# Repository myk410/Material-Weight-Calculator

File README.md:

# Material Weight Calculator

A standalone pocket calculator for estimating material weight. Select a material, enter length, width, and thickness in inches, and read the result in pounds. Runs entirely on one microcontroller with physical buttons and replaceable AAA batteries.

Status: **R3 LTC3440 buck-boost PCB implemented and CAD-validated, November 12, 2026; FABRICATION HOLD.** See [R3 review, evidence and unresolved physical checks](hardware/R3_REVIEW.md) and open [the R3 KiCad project](hardware/pcb/r3/material_weight_calculator.kicad_pro). Both current R3 boards use SMD resistors, capacitors, transistors, diodes and inductors; the purchased AVR DIP/socket and connectors are retained. See [owned-parts policy](hardware/OWNED_PARTS_AND_SMD.md). Main and display-adapter boards pass KiCad 9 ERC, DRC and schematic parity with zero violations. No R3 Gerbers/drills/order ZIP have been released because real-part mating and fit checks remain open. Existing R2 manufacturing archives use MCP1700 and must not be ordered as R3. Firmware, prototype operation and battery life remain untested.

## Proposed final low-power hardware

| Part | Proposed choice | Reason |
| --- | --- | --- |
| Controller | Microchip AVR128DA28, preferably the through-hole package for a hand-built prototype | One low-power microcontroller; enough RAM for a graphical display; internal oscillator; no wireless hardware needed |
| Display | EastRising ERC12864FS-655, 2.8-inch 128 × 64 positive monochrome LCD, no touch panel | Larger black-on-light screen; operate with backlight disconnected; separate UC1701 adapter PCB included |
| Buttons | Sixteen flexible-resin button caps over the user-owned DIYmalls 4 × 4 membrane keypad | Sixteen physical keys using eight controller pins; no separate keypad processor |
| Batteries | Three AAA alkaline cells in a replaceable holder | Switched supply; buck-boost conversion extends useful battery range, subject to diode drop and sag |
| Regulator | LTC3440EMS#PBF, MSOP-10, R3 | Nominal 3.3 V buck-boost with hand-solderable SMD supply components; see the R3 review for qualification limits |
| Supporting parts | Regulator input/output capacitors, local MCU decoupling, battery protection diode, display power transistor, service link, programming header | Reliable supply and a way to program the controller without leaving a USB interface powered |
| Housing | Rigid-resin printed calculator enclosure with accessible battery compartment | Large readable labels and easy battery replacement |

See [PARTS_LIST.md](PARTS_LIST.md) for previously purchased parts and the prototype route. The exact hardware R2 component and M2.5 fastener lists are in [hardware/README.md](hardware/README.md). The current R2 design uses the 70 × 50 mm EastRising display and a 70 × 18 mm adapter. The manufacturer lists up to 500 µA LCD current at 3.3 V; complete-device current and indoor readability still require a physical test.

The AVR128DA28 has 16 KB SRAM. A 128 × 64 monochrome framebuffer needs 1,024 bytes. PA1/PA2/PA3 drive clock/data/chip select, PA4 selects command/data, and PA5 resets the UC1701. The device needs firmware; the HTML calculator is a separate working example.

## Why memory LCD instead of e-paper?

| Display | Suitability |
| --- | --- |
| Reflective memory LCD | Recommended for calculator entry: quick digit updates, low power, readable by reflected light. Requires power and periodic display polarity inversion while displaying an image. |
| Black-and-white e-paper | Excellent for holding a result with display power removed. Updates are slower and may show ghosting or occasional full-screen flashes; partial-refresh behavior depends on the exact panel. |
| Reflective character LCD without a backlight | Worth considering if a cheaper, simpler text-only display is preferred. Select a specific low-power module before comparing total current; ordinary hobby modules are not all equally efficient. |

E-paper is compatible with a microcontroller and does not require a Raspberry Pi. For this device, fast keypad feedback makes memory LCD the stronger starting point. Neither unlit option is readable in darkness without external light.

## User operation

1. Press ON to wake the calculator.
2. Use MENU for material selection; 8/↑ and 2/↓ move through menus and ENTER selects. Default to the last material during the current powered session.
3. Choose solid rectangular stock or pipe using a short menu on the existing keypad.
4. For rectangular stock, enter length, width, and thickness in inches.
5. For pipe, enter length, actual outside diameter, and wall thickness (or inside diameter). Press ENTER after each input.
6. Show the material, dimensions, and estimated pounds, with the weight in the largest text.

Key functions: digits 0–9, decimal point, ENTER, MENU, BACK, CLEAR, and ON/OFF. This fits a 16-key matrix. The printed button caps will be made in rubbery resin, with recessed legends, and will actuate electrical switches underneath. See [MECHANICAL_DESIGN.md](MECHANICAL_DESIGN.md) for the key layout and printing requirements.

BACK deletes the last digit; with an empty field it returns to the previous field. CLEAR empties the current entry; on the result screen it starts a new piece while retaining the selected material and shape. ON/OFF puts the calculator to sleep. Do not use long-press combinations for routine entry. Start with decimal inches; fraction entry can be added if needed after testing the controls.

Reject empty fields, zero or negative dimensions, malformed numbers, overflow, and values beyond the supported input range. Display an explicit error instead of a plausible-looking weight. Always label the result as an estimate.

## Calculation and material data

For a solid rectangular piece:

`weight_lb = length_in × width_in × thickness_in × density_lb_per_ft3 / 1728`

Example using the published carbon-steel density of 7,850 kg/m³ (about 490.059 lb/ft³): a 12 × 12 × 1-inch plate weighs about 40.838 lb, displayed as `40.84 lb`.

The HTML now supports rectangular stock, pipe/round tube, and known volume. Pipe volume is `π × wall × (OD − wall) × length`, or equivalently `π/4 × (OD − ID) × (OD + ID) × length`. All dimensions are in decimal inches. Use actual diameters, not nominal pipe sizes. Pipe results exclude contents and fittings. Other hollow profiles and irregular parts need their own formulas.

At the user’s direction, the calculator replaces the company card values with published grade-specific densities. Material names now identify the grade, and separate presets cover LDPE/HDPE, 304/316 stainless, 718/625 nickel alloys, and 90/10 or 70/30 CuNi. Density overrides remain available for other grades. See [DENSITY_REVIEW.md](DENSITY_REVIEW.md) for active values, sources, and the historical card comparison. Do not use a broad material family as if every grade had the same density.

The handheld firmware should provide the same shape choices and density policy. Device firmware has not yet been implemented; the hardware pin map and power-control requirements are documented in hardware/README.md.

## Battery and sleep design

R3 uses three AAA alkaline cells through the physical slide switch, SS14 polarity diode and LTC3440 buck-boost supply. The regulated nominal output is 3.294 V. The converter's 2.5 V minimum applies at its VIN pin **after diode loss and battery sag**. The current EastRising UC1701 display is supplied from this rail through Q1; it has no Sharp-breakout regulator in this path.

The LTC3440's typical Burst Mode quiescent current is 25 µA, and the output divider adds about 6.1 µA. R3 therefore does not meet the old sub-10-µA automatic-sleep goal with its rail running; MCU and other leakage add to this. The slide switch provides hard battery disconnection. Whole-device current, stability and runtime remain unmeasured.

- While active, scan/debounce keys and update the UC1701 framebuffer. This display does not use the former Sharp memory-LCD VCOM servicing scheme.
- After about two minutes without input, save current state in RAM, blank the display, shut the display down according to its documentation, disable unused peripherals, and enter MCU power-down mode.
- If display power is switched off, put connected signal pins in a safe state to prevent back-powering. Reinitialize and redraw on wake.
- Wake from a keypad interrupt. In sleep, drive matrix columns low and use pulled-up interrupt-capable row inputs. Confirm exact AVR pin wake behavior before assigning pins. Consume the wake press so it does not enter a stray digit. Wait for key release before accepting another entry.
- Avoid continuous keypad polling during sleep, always-on LEDs, powered USB adapters, and continuously connected battery-sense resistor dividers.
- The case-mounted CYT1107 slide switch disconnects battery positive before main-board J2 pin 1; battery negative goes to J2 pin 2. JP1 remains an internal service link with its shunt normally fitted. The keypad ON/OFF key controls sleep only while the slide switch is ON. Hard power-off loses RAM state. See [power-switch wiring](hardware/POWER_SWITCH.md).

Battery-life estimates must use measured current for the complete assembly, including converter, divider, MCU and display. The former sub-10-µA automatic-sleep target is superseded by the R3 supply budget above; active current is also unverified.

Illustrative budget only: at 5 mA for 20 minutes per day plus 10 µA for the rest of the day, consumption is about 1.90 mAh/day. An assumed usable pack capacity of 800 mAh gives about 420 days arithmetically. Real runtime will depend on cutoff voltage, cell type, regulator dropout, temperature, leakage, and usage. Series-connected AAA cells raise voltage; their mAh capacities do not add.

## Build sequence

1. Confirm a readable display size and source the exact module.
2. Prototype the controller, display, and relabeled keypad. Use a detachable UPDI programmer; it is a setup tool, not part of the running device.
3. Implement the material menu, three input fields, calculation, and input validation. Check known rectangular-stock examples and custom density.
4. Implement keypad wake and display shutdown. Measure whole-device active and sleep current from the battery input.
5. Validate operation over the usable battery voltage range, including low-battery indication and clean handling of power loss.
6. Finalize the schematic, component list, firmware build instructions, and enclosure after these checks.

## Manufacturer references

- [Microchip AVR128DA28](https://www.microchip.com/en-us/product/AVR128DA28) and its linked datasheet: voltage limits, memory, sleep behavior, pin functions, and programming.
- [Analog Devices LTC3440](https://www.analog.com/en/products/ltc3440.html) and its linked datasheet: R3 regulator topology, pinout, compensation, layout and high-input protection. The preserved R2.1 design used MCP1700.
- [Waveshare e-paper manual](https://www.waveshare.com/wiki/2.13inch_e-Paper_HAT_Manual): refresh and standby considerations for an alternative display.
- [ATI corrosion-resistant titanium datasheet](https://www.atimaterials.com/Products/Documents/datasheets/titanium/alloyed/ati_corrosion_resistant_titanium%20_alloys_tds_en5_v1.pdf): grade-specific titanium density.

## Validation

Run `node tests/calculator.test.cjs` to check rectangular and pipe formulas, equivalent wall/ID inputs, published grade densities and replacement of the titanium misprint, input validation, override labeling, and mocked UI transitions. These checks pass. A real-browser check could not run in the current environment because the Chromium executable is unavailable; browser rendering and physical hardware remain unverified.

The display pin map, electrical source references, adapter BOM and 128 × 64 screen-layout requirements are in [hardware/DISPLAY_INTEGRATION.md](hardware/DISPLAY_INTEGRATION.md).

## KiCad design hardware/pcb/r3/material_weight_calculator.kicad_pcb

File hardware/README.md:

# Material Weight Calculator — current R3 review

**FABRICATION HOLD.** The current LTC3440 MSOP-10 design is in [pcb/r3](pcb/r3/material_weight_calculator.kicad_pro). Read [R3_REVIEW.md](R3_REVIEW.md) for the circuit, actual KiCad results, both-side orientation templates, BOM and required physical evidence. Both current R3 boards use SMD resistors, capacitors, transistors, diodes and inductors; the purchased AVR DIP/socket and connectors are retained. See [owned-parts policy](OWNED_PARTS_AND_SMD.md). Main/adapter ERC, DRC and schematic parity pass with zero violations. No R3 Gerbers, drills or order ZIP are released. The R2 files and links below are historical MCP1700 designs, not the R3 supply, and must not be used for this redesign.

## Historical R2.1 documentation

PCB review updated November 2, 2026: [review, evidence and assembly gates](PCB_REVIEW.md). Open the reviewed PCB files with **KiCad 9 or newer**. The download filenames retain `r2` for existing links; their fabrication contents identify R2.1. Mechanical files retain their separate revision history.

This package contains real parametric CAD, printable STLs, a routed KiCad PCB, schematic, Gerbers, drills, and actual-scale print templates. It is a **prototype design**, not a physically tested or production-qualified assembly. The device firmware is not included in this hardware release; its revised 128 × 64 display and sleep requirements are specified in DISPLAY_INTEGRATION.md. R2 replaces the small Sharp display. R1 files remain in Git history, not in current print/download folders.

Download [complete R2 package](downloads/material_weight_calculator_hardware_r2.zip) or [both PCB fabrication sets](downloads/pcb_fabrication_r2.zip).

## Start here

1. Open `docs/case_front_preview.png` to inspect the actual CAD and recessed legends.
2. Print `docs/keypad_fit_template.pdf` at **100% / Actual Size**. Place the existing DIYmalls pad over the key-center marks. The screenshot identifies the pad type but does not establish its exact pitch. The model currently uses nominal 18 mm key pitch; confirm this fit before printing the full shell. The source has explicit `KEY_X` and `KEY_Y` parameters if the actual pad differs.
3. Print the two-key connected 55A keypad coupon before the full keypad sheet. Check legend detail, independent motion, return, actuator contact, nut fit, and actuation with the actual DIYmalls membrane. No claim is made that the 55A resin's force, shrinkage, or long-term fatigue has been physically validated yet.
4. For the Mars 5 Ultra, use the shell sections in `stl/mars5_ultra_oriented/`. They have been rotated to fit the manufacturer's 153.36 × 77.76 × 165 mm build volume; add supports and a raft in the slicer without exceeding that volume. These are unsliced STLs, not exposure profiles.
5. Historical R2.1 only; **do not order these for R3**. `pcb/gerbers/` describes a conventional **two-layer, 1.6 mm copper-clad PCB with plated through holes**. Open the KiCad project to inspect/edit it before ordering.

## Files

| Location | Contents |
| --- | --- |
| `stl/` | Four case sections, battery cover, keypad plates, display cradle, **one-piece 55A flexible keypad sheet**, and fit coupons |
| `stl/mars5_ultra_oriented/` | Printer-fitting orientations for the shell sections and larger keypad plates |
| `cad/calculator_assembly.step` | Assembly with parts in their assembled locations; split case sections included |
| `cad/pcb_outline.step` | Board outline and four mounting holes, matching the enclosure |
| `cad/*whole_reference.stl` | Unsplit shell references for a larger printer; do not use these on the Mars 5 Ultra |
| `source/build_case.py` | Editable CadQuery source for case, one-piece keypad sheet, nut pockets, and split shells |
| `pcb/material_weight_calculator.kicad_pro` | KiCad 9 project |
| `pcb/material_weight_calculator.kicad_sch` | Editable, embedded-symbol schematic with every used pin/net explicitly named |
| `pcb/material_weight_calculator.kicad_pcb` | Routed two-layer board, 82 × 68 mm |
| `pcb/mw-footprints.pretty/` | Bundled standard footprints; project does not depend on an external footprint-library path |
| `pcb/gerbers/` | Top/bottom copper and masks, top silkscreen, outline, separate plated/non-plated Excellon drills and SVG drill maps |
| `docs/copper_artwork_1to1.pdf` | Exact KiCad copper plots: top reference, top transfer, bottom reference, bottom transfer |
| `docs/drill_template.pdf` | Component-side drill and board outline template |
| `docs/keypad_fit_template.pdf` | Full-scale membrane alignment template and 100 mm scale check |
| `docs/schematic.pdf` | Circuit drawing exported by KiCad |
| `pcb/bom.csv` | Main-board BOM |
| `pcb/display_adapter/` | Second KiCad project, schematic, routed 70 × 18 mm adapter and BOM |
| `docs/display_adapter_schematic.pdf` | Adapter circuit, exported by KiCad |
| `docs/display_adapter_copper_1to1.pdf` | Four actual-scale copper reference/transfer pages |
| `docs/display_adapter_drill.pdf` | Adapter drill/outline template at actual size |
| `docs/display_fit_template.pdf` | Full-scale 70 × 50 mm module and pin-center alignment check |
| `DISPLAY_INTEGRATION.md` | Authoritative R2 display pin map, sources and firmware requirements |
| `validation/` | CAD, mesh, schematic-net and KiCad design-rule reports |

The STLs are in millimeters, not mirrored. Each individual file is translated to its own positive bounding box. Use STEP for assembly positions. The old loose-button aggregate `all_16_buttons.stl` is obsolete; rebuilding the current source deletes it and exports `keypad_sheet_55A.stl` instead. No support structures are baked into the meshes.

## One-piece 55A keypad

The custom visible keypad is now **one connected flexible-resin part**, not sixteen loose buttons. The CAD nominally uses a 72 × 72 × 0.85 mm continuous sheet behind the 4 × 4 button field. Each key has a 14 × 14 mm top rising about 5 mm above that sheet, plus a centered smooth 8 mm-diameter actuator projecting about 1.55 mm below it.

The thin sheet is the flex zone. The thicker key tops remain individual islands geometrically, but they are permanently joined by the 0.85 mm membrane. This should reduce assembly parts, keep the key field aligned, and provide a continuous dust barrier over the original electrical membrane. The dimensions are prototype targets and should be tuned after the first real 55A print.

The existing DIYmalls 4 × 4 pad remains the **electrical switch layer** underneath. The printed 55A part is only the custom mechanical keypad. Do not assume the printed resin is conductive.

## Case and fasteners

Overall body: 96 × 184 × 31 mm, with button tops at about 33 mm. Wall/face thickness is generally 2.6 mm, with internal reinforcement webs. The PCB's lower face is 7 mm from the rear reference plane. The holder pocket targets a Pololu 1144-style 52 × 37 × 13 mm three-AAA holder with leads, allowing clearance around that envelope.

All fastening provisions are **M2.5 with hex nuts**, as requested. Nominal nut pockets are 5.35 mm across flats and about 2.45 mm deep; clearance holes are 2.9 mm. Glue nuts around their outside faces, keeping threads and screw paths clean. On front-facing pocket openings, hold the nut flush to the pocket's open face while the adhesive sets, rather than pushing it deeper into the clearance allowance. Verify actual nut dimensions with the coupon before gluing the full set.

| Joint | Screws | Nuts |
| --- | --- | --- |
| Rear to front shell | 4 × M2.5 × 16 mm | 4, glued into front-shell pockets |
| PCB to rear posts | 4 × M2.5 × 6 mm | 4, glued into rear-post pockets |
| Keypad backing + guide stack to front | 4 × M2.5 × 6 mm | 4, glued into front pockets |
| Display cradle to front | 4 × M2.5 × 6 mm | 4, glued into front pockets |
| Battery cover | None; sliding rails and snap latch | None |

Total: **16 nuts; four 16 mm and twelve 6 mm screws**. Screw lengths are measured under the head. Trial-fit and shorten any screw that bottoms before clamping; do not force a screw into resin. The design does not use heat-set inserts or self-tapping threads.

The long front and rear shells each have an upper/lower **bonded seam** at plan Y=60.25 mm, with locating tongues and mating relief. Bond each upper/lower pair into one shell before final assembly. This printing seam is separate from the removable, screwed front/rear joint. Use an adhesive appropriate for the fully cured rigid resin and test it on a coupon. One-piece references are included if a larger printer is available.

## Assembly order

1. Wash/cure the printed parts according to the actual resin's instructions. Clear supports from recesses and mating faces. Bond the two front sections and the two rear sections using their locating features.
2. Test-fit and glue the M2.5 nuts into their pockets. Allow adhesive to set before applying screw load.
3. From inside the front, place the **single connected 55A keypad sheet** behind all sixteen bezel openings at once. Align its sixteen button tops with the openings. The 0.85 mm connecting membrane remains behind the bezel and keeps the entire keypad registered as one piece. Legends are actual 0.4 mm Boolean recesses, not rendered textures.
4. Install the rigid guide/backing stack and the existing DIYmalls electrical membrane underneath the printed keypad. The guide acts as registration and a travel-stop layer while the thin printed sheet provides key return. The current actuator projection and rest/stop values are prototype geometry only; verify that the electrical pad is not preloaded at rest and that each key returns without dragging its neighbors.
5. Route the electrical membrane's flexible ribbon through the backing relief; avoid sharp folds or pinching at the enclosure edge. The backing's screw slots allow small translational adjustments, not arbitrary correction of key pitch.
6. Use the ERC12864FS-655 **without touch panel**. Its body fits at plan (13,7.5), 70 × 50 × 5.8 mm maximum. The 67 × 37 mm bezel opening follows the drawing's viewing-area offset: 1.5 mm from the left and 3.5 mm from the top. Place thin 0.5 mm closed-cell foam on opaque perimeter/frame surfaces, between the front shell and module and between the module's backlight frame and rear cradle. Fit the cradle with four M2.5 × 6 mm screws. Tighten only enough to retain it; do not compress LCD glass, the polarizer or the solder tail. No separate printed edge clamps are used in R2.
   Assemble the display adapter before installing the cradle. J2 is a **1×22 row at 1.27 mm pitch**, not 2.54 mm. Solder the module's own pins directly into the adapter holes; do not add another tall header/socket. Keep the adapter at nominal Z=13 to 14.6 mm behind the top tail. Check pin-1 orientation against the manufacturer's front-view drawing. Use short insulated wires at adapter J1 rather than a tall plug. Secure the cable to the cradle side with a soft tie/adhesive anchor, without loading the glass. Capacitor C5 must be ≤4 mm diameter and ≤7 mm high; C1/C2 ≤5.5 mm high and remaining adapter parts ≤5 mm high. Confirm actual pin reach before soldering; the fit template provides the 22 pin centers.
7. Assemble the PCB, check power rails with U1/display disconnected, fit the socketed MCU, then connect the keypad, display cable, and battery holder using the wiring below.
8. Install the PCB in the rear tray, secure the battery holder in its pocket, and route leads clear of nut pockets and ribs. Install the battery cover, then join front/rear with the four longer screws.

## PCB circuit and parts

| Ref | Part / function | Quantity |
| --- | --- | ---: |
| U1 | AVR128DA28-I/SP, in 28-pin narrow DIP socket (7.62 mm row spacing) | 1 + socket |
| U2 | MCP1700-3302E/TO, 3.3 V LDO; spread-lead TO-92 footprint | 1 |
| D1 | 1N5817, DO-41, battery reverse-polarity protection | 1 |
| Q1 | onsemi 2N3906 PNP, E-B-C pins 1-2-3, TO-92 spread leads; switches display power | 1 |
| R1 | 10 kΩ, axial, 7.62 mm lead spacing | 1 |
| R2 | 100 kΩ, axial, 7.62 mm lead spacing | 1 |
| C1, C2, C5 | TDK FG14X7R1H225KRT00, 2.2 µF 50 V X7R, 2.5 mm pitch; body ≤4.5 × 3.0 mm, height ≤5.5 mm | 3 |
| C3, C4 | 100 nF, at least 10 V, ceramic, 2.5 mm lead spacing | 2 |
| J1 | 1×8, 2.54 mm male header to existing keypad tail | 1 |
| J2 | 1×2, 2.54 mm battery-lead connector; observe polarity | 1 |
| JP1 | 1×2, 2.54 mm header and shunt, normally fitted master/service link | 1 |
| J3 | 1×8, 2.54 mm header to display via cable | 1 |
| J4 | 1×3, 2.54 mm UPDI programming header | 1 |
| External | Existing membrane keypad, ERC12864FS-655 display and R2 adapter, three-AAA holder and cells, wiring | 1 set |

No USB interface, radio, indicator LED or charging circuit is on this board. It uses alkaline AAA cells. D1 adds a small forward drop, so regulation ends earlier in battery discharge than with an ideal-diode design. The case-mounted CYT1107 slide switch is the primary hard ON/OFF control, wired before J2 pin 1; J2 pin 2 is battery negative. JP1 remains a normally fitted internal service link. The keypad ON/OFF key provides sleep/wake only while hard power is ON. See POWER_SWITCH.md. Hard OFF removes the battery source, but a connected powered UPDI programmer can still power the board.

Q1 is off at reset through R2. Firmware must drive U1 PD7 **low** to enable display power and **high** to turn it off. Before removing display power, drive all display signal outputs low to prevent back-powering, then redraw/reinitialize on wake. UC1701 maintains LCD drive internally while powered; no Sharp-style VCOM servicing is used. Reset and reinitialize the UC1701 after each display power cycle. Use PA4 for command/data and PA5 for active-low LCD reset. Disable unused peripherals and configure unused MCU pins appropriately; whole-device sleep current is not yet measured.

### Connector wiring

J1 pins 1–4 are assigned ROW0–ROW3 on PC0–PC3; pins 5–8 are COL0–COL3 on PD0–PD3. Membrane tail row/column ordering varies: establish the actual mapping by continuity test or a key-scan test, then map the eight signal assignments in firmware. Do not assume the photo supplies the electrical pinout.

| Main J3 / adapter J1 pin | Function | MCU |
| ---: | --- | --- |
| 1 | Switched 3.3 V LCD_VCC | Q1 collector |
| 2 | GND | Ground |
| 3 | SCK | PA1, DIP pin 23 |
| 4 | SDA | PA2, DIP pin 24 |
| 5 | CS, active low | PA3, DIP pin 25 |
| 6 | CD: low command, high pixels | PA4, DIP pin 26 |
| 7 | RST, active low | PA5, DIP pin 27 |
| 8 | No connection; spare position | No wire |

Connect matching **pin numbers** between main J3 and adapter J1. These are seven wires on an eight-position footprint. No part of this cable is compatible with R1's Sharp wiring. The adapter straps BM1/BM0, WR0/WR1 and unused D0–D5 to ground, and provides the LCD charge-pump capacitors. Leave the separate backlight A/K terminals insulated and unconnected.

Adapter BOM: C1/C2 = TDK FG14X7R1H225KRT00, 2.2 µF 50 V X7R (2.5 mm pitch, 4.5 × 3.0 mm body, height ≤5.5 mm), C3 = 330 nF 25 V ceramic, C4 = 100 nF, C5 = 10 µF 16 V low-leakage electrolytic (4 mm diameter, 1.5 mm pitch, ≤7 mm height), R1 = 10 MΩ axial. The two flying capacitors bridge VB0+/VB0− and VB1+/VB1−; C3 and R1 connect VLCD to ground. See the separate adapter schematic, BOM and DISPLAY_INTEGRATION.md.
J4 pin 1 is +3.3 V / VTREF, pin 2 GND, pin 3 UPDI. A suitable example programmer is **Adafruit UPDI Friend 5879**, set to **3V**. Disconnect the AAA pack when powering the target from the programmer. Do not connect two independent supplies together. The CANADUINO ATmega328P automatic bootloader programmer is not compatible with this MCU.

### Existing pad labels to custom keys

| Original pad row | Custom button functions in the same physical positions |
| --- | --- |
| 1, 2, 3, A | 7, 8/Up, 9, MENU |
| 4, 5, 6, B | 4, 5, 6, BACK |
| 7, 8, 9, C | 1, 2/Down, 3, CLEAR |
| *, 0, #, D | ON/OFF, 0, decimal point, ENTER/= |

## Fabrication and printing

For a PCB manufacturer, use the Gerbers and separate PTH/NPTH drill files, specify **82 × 68 mm, 2 layers, 1.6 mm FR-4**, and retain plated holes. Fabricate the **70 × 18 mm adapter** as a separate 2-layer, 1.6 mm FR-4 board from `pcb/display_adapter/gerbers/`. The fabrication ZIP has a separate directory for each board; do not combine their layers. All tracks are 0.4 mm wide; minimum configured clearance is 0.25 mm; both boards use through vias, 1.0 mm diameter / 0.5 mm drill (actual counts in their design JSON files). Standard footprint holes retain their own drill diameters. The board mounting holes are 2.7 mm nominal; the resin clearance holes are 2.9 mm.

For home etching, the copper PDF includes labeled reference and transfer orientations. Print 100%, verify the 100 mm scale, and register both layers accurately. Home-drilled holes are not automatically plated: every via and any PTH joining layers requires a conductive connection soldered on both sides. DIP sockets and headers can obstruct top-side soldering, so use accessible raised/machined contacts or a professionally plated board. Exact Gerbers are authoritative; the PDFs are for manual processes.

Ordinary printing resin forms the housing and keypad, **not conductive PCB traces**. The PCB files describe copper on an insulating board. No resin-printer exposure file, printer-specific sliced file, or CNC isolation toolpath is supplied because those depend on the actual fabrication process and tools.

The STLs are unsliced. Use rigid resin for housing, cradle and plates; use **55A flexible resin for `keypad_sheet_55A.stl`**. Keep supports away from label recesses, screw bores, nut pockets, actuator faces and mating surfaces. The keypad sheet is only 0.85 mm thick between keys, so avoid support placement or cleanup methods that can tear or permanently distort the flex zones. Optional compatible paint-fill can improve legend contrast. Hollow shell cavities must remain accessible for washing and curing; orient them to drain.

## What was verified

- Each individual CAD part in the prior R2 build was a valid, single solid.
- Each exported STL in the prior R2 build had a closed two-use edge graph at the mesh-check precision.
- Pairwise assembled-part checks in the prior R2 build found no positive intersections above 0.02 mm³ (nominal, unloaded geometry).
- Exported schematic pin-to-net connections match the PCB design definition, normalizing the root-sheet prefix on local net names.
- R2.1 KiCad 9.0.2 reports: **0 ERC violations, 0 DRC violations, 0 unconnected items and 0 schematic parity issues**, on both boards. Symbols have electrical pin types and bundled project libraries. See `validation/pcb_audit.json` for the actual-pad/copper and case-hole audit.
- PCB outline/mount-hole positions and case PCB posts share the same design coordinates.
- **The new one-piece 55A keypad source has not yet been physically printed or re-validated as an exported mesh in this commit.** Rebuild the CAD and inspect `validation/cad_checks.json` before treating the generated keypad STL as final.
- Actual keypad pitch, cured-resin tolerances, membrane actuation, display pin fit/ambient-light contrast, soldered component heights, electrical operation and battery runtime still need physical confirmation. Computational checks do not replace an electrical bench test or an independent hardware review.

## Rebuilding

Use CadQuery 2.7 / OpenCascade for `python source/build_case.py`. The current source exports `stl/keypad_sheet_55A.stl`, a two-key 55A fit coupon, and removes obsolete loose-button STLs from older builds. `source/check_and_render.py` also rebuilds the CAD, checks meshes and net mappings, and draws previews. For the current reviewed boards, run `source/refresh_schematics.py`, then `source/export_pcbs.py` and `source/audit_pcb.py` using KiCad 9 Python bindings and CLI. The original `build_pcb.py` and `build_display_adapter.py` routing generators rebuild copper from scratch and call the schematic refresh afterward; a fresh routed build requires a new full audit. Prefer refresh for metadata/schematic changes so the reviewed copper is retained. Run `source/validate_display.py` for the manufacturer pin/capacitor audit. Export both schematic netlists before running the net checks. `source/plot_copper.py` uses KiCad's native plot controller for exact copper artwork. `source/make_print_templates.py` requires ReportLab. Plot main copper with `source/plot_copper.py`, then again with `DISPLAY_ADAPTER=1`; run `source/finish_exports.py` last to assemble labeled PDFs, verify both netlists and package R2 ZIPs.

## Source references

- [AVR128DA28 datasheet, pinout and SPDIP package](https://ww1.microchip.com/downloads/aemDocuments/documents/MCU08/ProductDocuments/DataSheets/AVR128DA28-32-48-64-Data-Sheet-DS40002183.pdf).
- [MCP1700 datasheet, TO-92 pinout and capacitor requirements](https://ww1.microchip.com/downloads/en/DeviceDoc/MCP1700-Data-Sheet-20001826F.pdf).
- [ERC12864FS-655 product](https://www.buydisplay.com/2-8-inch-128x64-graphic-module-serial-display-spi-lcd-w-optl-touch-screen).
- [EastRising module datasheet](https://www.buydisplay.com/download/manual/ERC12864-655_Series_Datasheet.pdf) and [SPI reference circuit](https://www.buydisplay.com/download/interfacing/ERC12864-655_Interfacing.pdf). See DISPLAY_INTEGRATION.md for the drawing and pin audit.
- [Pololu 1144 three-AAA holder envelope](https://www.pololu.com/product/1144).
- [Adafruit UPDI Friend](https://www.adafruit.com/product/5879).
- [ELEGOO Mars 5 Ultra build volume](https://us.elegoo.com/products/mars-5-ultra-9k-7inch-monochrome-lcd-resin-3d-printer).
- Standard footprints were copied from KiCad 7 libraries; the R2.1 radial capacitor footprint is project-created. see `pcb/FOOTPRINT_LICENSE.txt`.

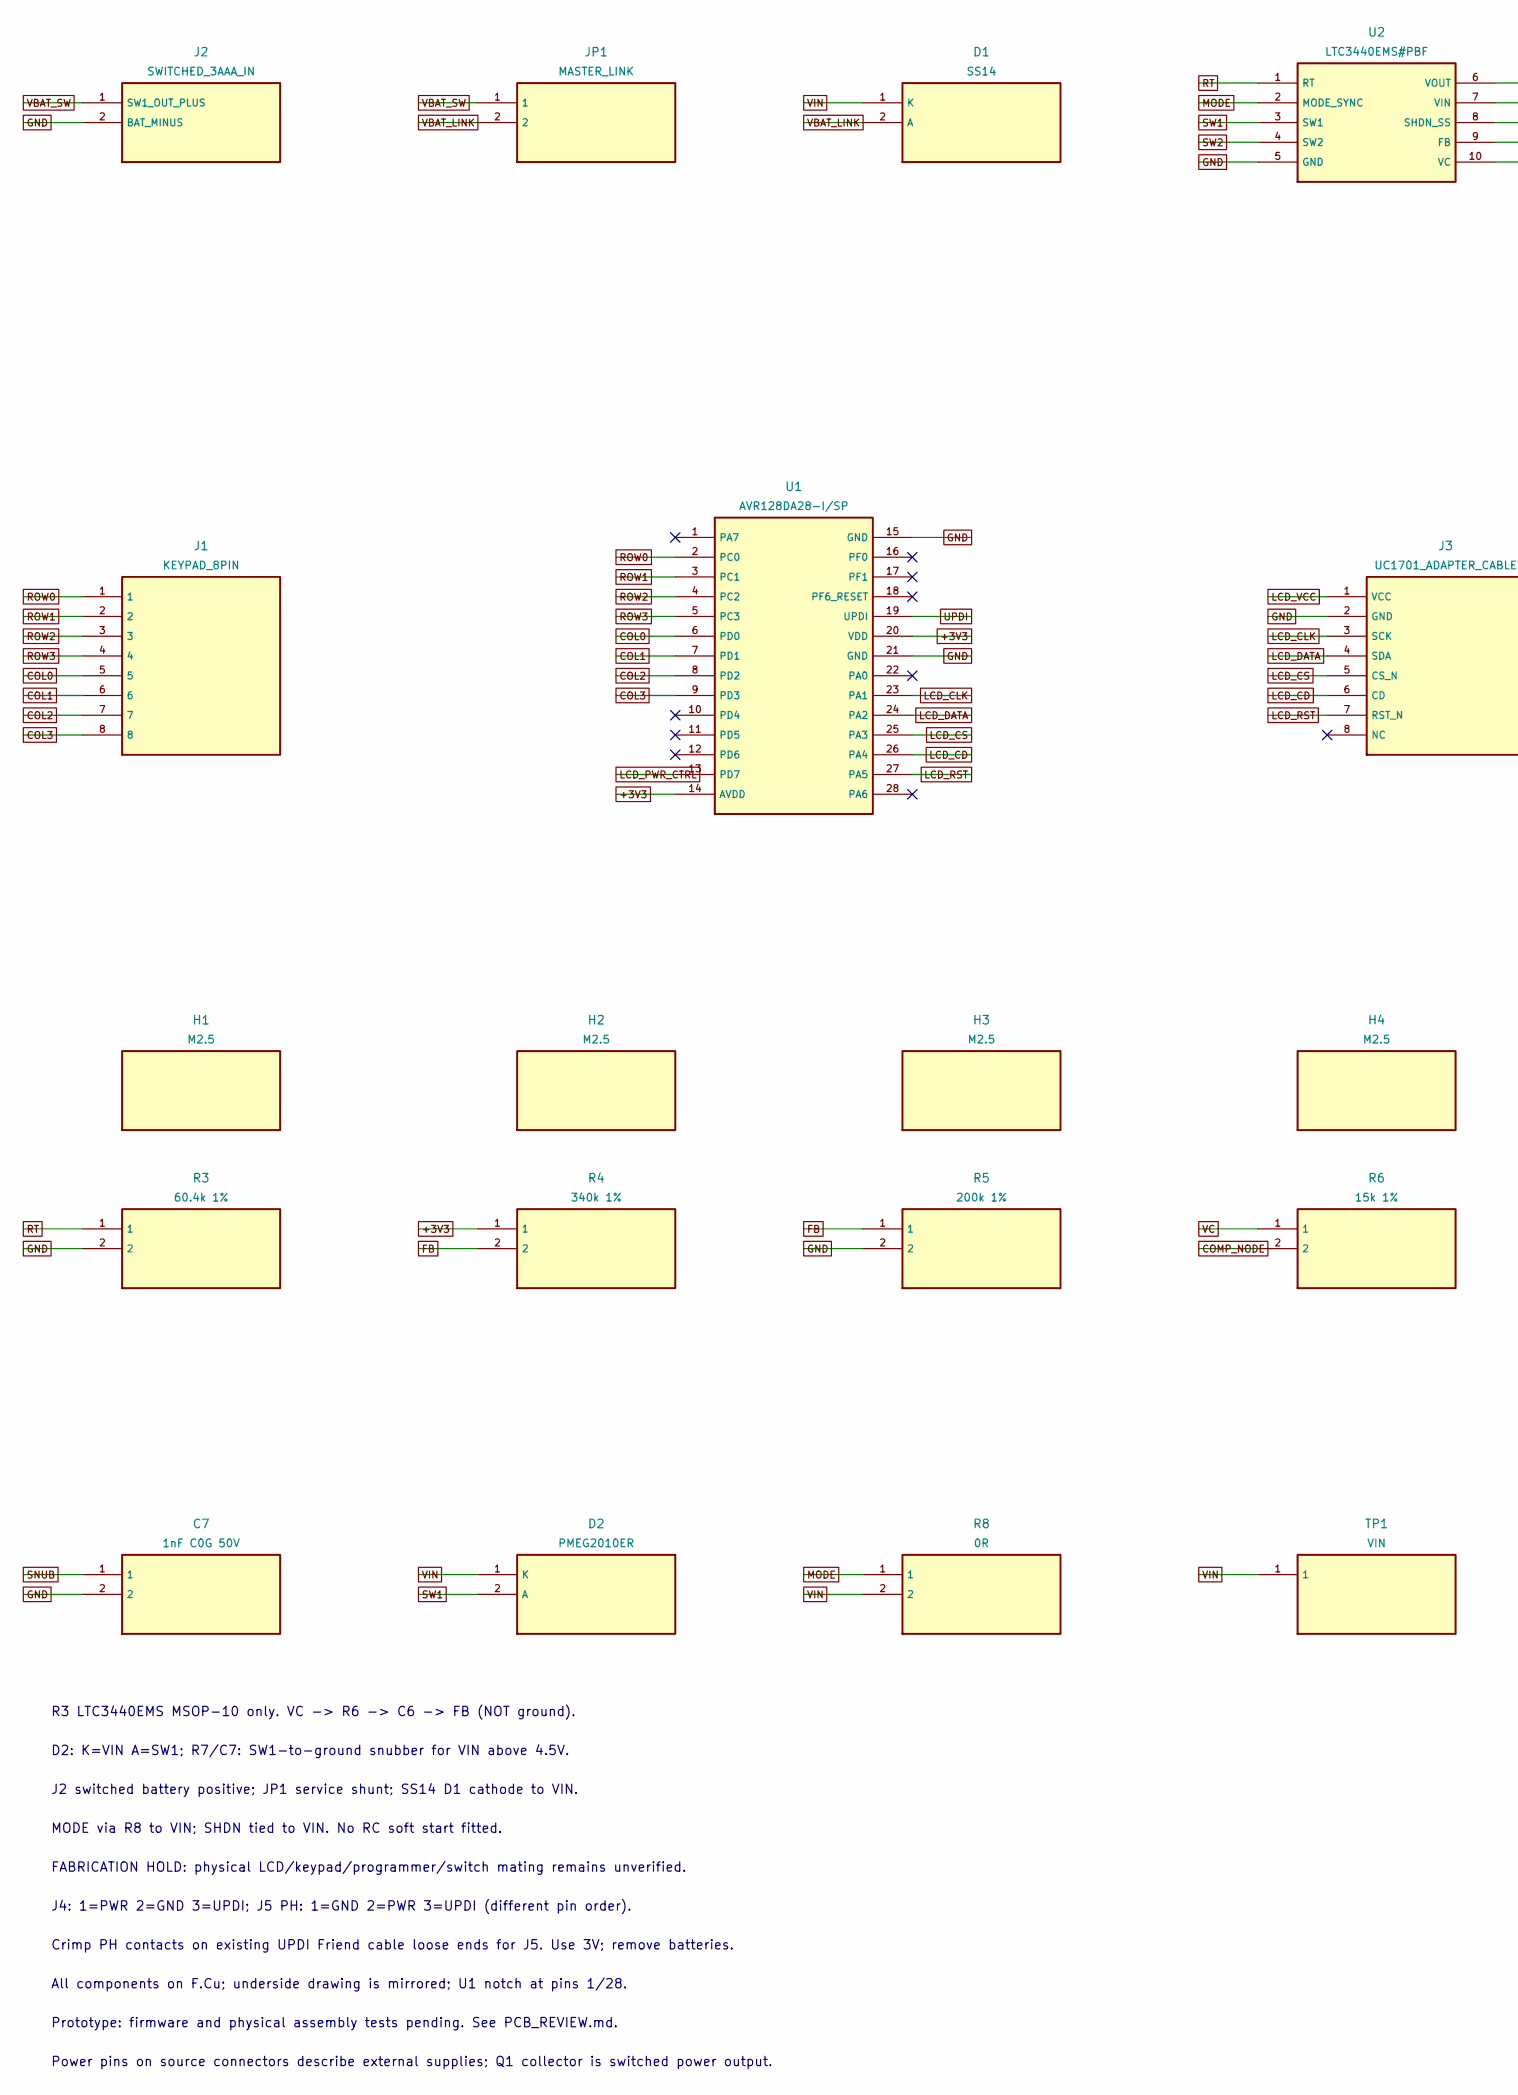
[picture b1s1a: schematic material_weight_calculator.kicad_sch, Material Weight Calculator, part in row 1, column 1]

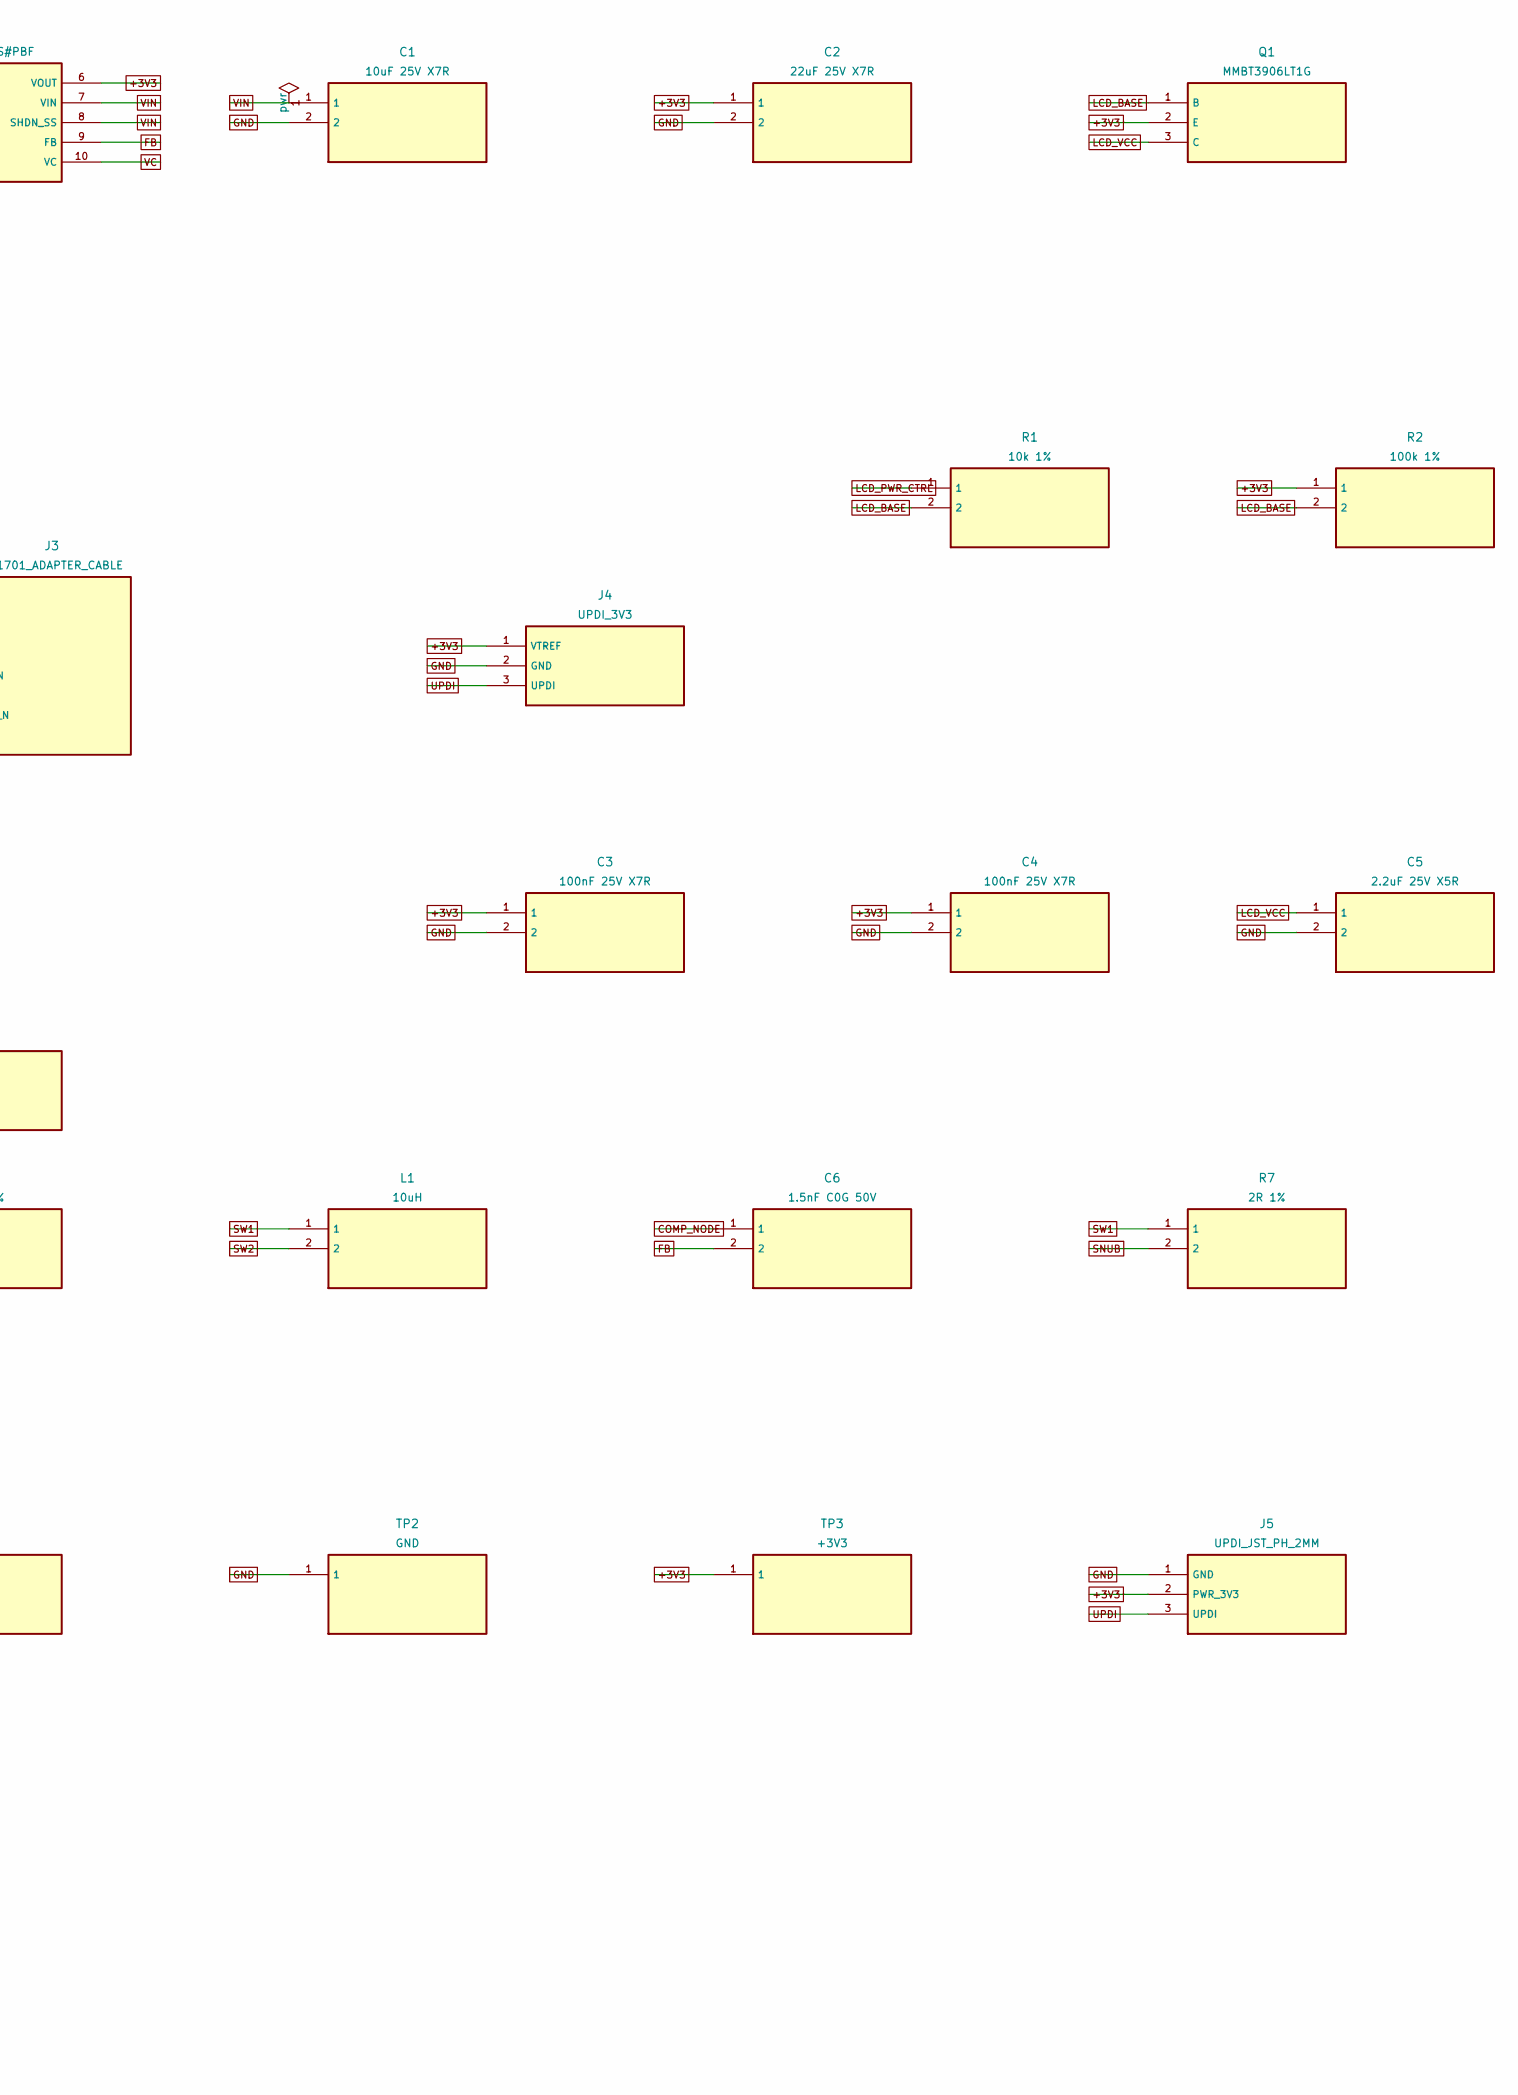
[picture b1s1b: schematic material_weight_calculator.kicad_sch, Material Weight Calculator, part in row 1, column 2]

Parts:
C1: 10uF 25V X7R; C_1206_3216Metric_Pad1.33x1.80mm_HandSolder
C2: 22uF 25V X7R; C_1210_3225Metric_Pad1.33x2.70mm_HandSolder
C3, C4: 100nF 25V X7R; C_0603_1608Metric_Pad1.08x0.95mm_HandSolder
C5: 2.2uF 25V X5R; C_0603_1608Metric_Pad1.08x0.95mm_HandSolder
C6: 1.5nF C0G 50V; C_0805_2012Metric_Pad1.18x1.45mm_HandSolder
C7: 1nF C0G 50V; C_0805_2012Metric_Pad1.18x1.45mm_HandSolder
D1: SS14; D_SMA
D2: PMEG2010ER; Nexperia_CFP3_SOD-123W
H1, H2, H3, H4: M2.5; MountingHole_2.7mm_M2.5
J1: KEYPAD_8PIN; PinHeader_1x08_P2.54mm_Vertical
J2: SWITCHED_3AAA_IN; PinHeader_1x02_P2.54mm_Vertical
J3: UC1701_ADAPTER_CABLE; PinHeader_1x08_P2.54mm_Vertical
J4: UPDI_3V3; PinHeader_1x03_P2.54mm_Vertical
J5: UPDI_JST_PH_2MM; JST_PH_B3B-PH-K_1x03_P2.00mm_Vertical
JP1: MASTER_LINK; PinHeader_1x02_P2.54mm_Vertical
L1: 10uH; L_CDRH6D38_HandSolder
Q1: MMBT3906LT1G; SOT-23_Handsoldering
R1: 10k 1%; R_0603_1608Metric_Pad0.98x0.95mm_HandSolder
R2: 100k 1%; R_0603_1608Metric_Pad0.98x0.95mm_HandSolder
R3: 60.4k 1%; R_0805_2012Metric_Pad1.20x1.40mm_HandSolder
R4: 340k 1%; R_0805_2012Metric_Pad1.20x1.40mm_HandSolder
R5: 200k 1%; R_0805_2012Metric_Pad1.20x1.40mm_HandSolder
R6: 15k 1%; R_0805_2012Metric_Pad1.20x1.40mm_HandSolder
R7: 2R 1%; R_0805_2012Metric_Pad1.20x1.40mm_HandSolder
R8: 0R; R_0805_2012Metric_Pad1.20x1.40mm_HandSolder
TP1: VIN; TestPoint_Pad_D2.0mm
TP2: GND; TestPoint_Pad_D2.0mm
TP3: +3V3; TestPoint_Pad_D2.0mm
U1: AVR128DA28-I/SP; DIP-28_W7.62mm
U2: LTC3440EMS#PBF; MSOP-10_3x3mm_P0.5mm

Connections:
+3V3: C2.1, C3.1, C4.1, J4.1 (VTREF), J5.2 (PWR_3V3), Q1.2 (E), R2.1, R4.1, TP3.1, U1.14 (AVDD), U1.20 (VDD), U2.6 (VOUT)
COL0: J1.5, U1.6 (PD0)
COL1: J1.6, U1.7 (PD1)
COL2: J1.7, U1.8 (PD2)
COL3: J1.8, U1.9 (PD3)
COMP_NODE: C6.1, R6.2
FB: C6.2, R4.2, R5.1, U2.9 (FB)
GND: C1.2, C2.2, C3.2, C4.2, C5.2, C7.2, J2.2 (BAT_MINUS), J3.2 (GND), J4.2 (GND), J5.1 (GND), R3.2, R5.2, TP2.1, U1.15 (GND), U1.21 (GND), U2.5 (GND)
LCD_BASE: Q1.1 (B), R1.2, R2.2
LCD_CD: J3.6 (CD), U1.26 (PA4)
LCD_CLK: J3.3 (SCK), U1.23 (PA1)
LCD_CS: J3.5 (CS_N), U1.25 (PA3)
LCD_DATA: J3.4 (SDA), U1.24 (PA2)
LCD_PWR_CTRL: R1.1, U1.13 (PD7)
LCD_RST: J3.7 (RST_N), U1.27 (PA5)
LCD_VCC: C5.1, J3.1 (VCC), Q1.3 (C)
MODE: R8.1, U2.2 (MODE_SYNC)
ROW0: J1.1, U1.2 (PC0)
ROW1: J1.2, U1.3 (PC1)
ROW2: J1.3, U1.4 (PC2)
ROW3: J1.4, U1.5 (PC3)
RT: R3.1, U2.1 (RT)
SNUB: C7.1, R7.2
SW1: D2.2 (A), L1.1, R7.1, U2.3 (SW1)
SW2: L1.2, U2.4 (SW2)
UPDI: J4.3 (UPDI), J5.3 (UPDI), U1.19 (UPDI)
VBAT_LINK: D1.2 (A), JP1.2
VBAT_SW: J2.1 (SW1_OUT_PLUS), JP1.1
VC: R6.1, U2.10 (VC)
VIN: C1.1, D1.1 (K), D2.1 (K), R8.2, TP1.1, U2.7 (VIN), U2.8 (SHDN_SS)

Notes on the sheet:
R3 LTC3440EMS MSOP-10 only. VC -> R6 -> C6 -> FB (NOT ground).
D2: K=VIN A=SW1; R7/C7: SW1-to-ground snubber for VIN above 4.5V.
J2 switched battery positive; JP1 service shunt; SS14 D1 cathode to VIN.
MODE via R8 to VIN; SHDN tied to VIN. No RC soft start fitted.
FABRICATION HOLD: physical LCD/keypad/programmer/switch mating remains unverified.
J4: 1=PWR 2=GND 3=UPDI; J5 PH: 1=GND 2=PWR 3=UPDI (different pin order).
Crimp PH contacts on existing UPDI Friend cable loose ends for J5. Use 3V; remove batteries.
All components on F.Cu; underside drawing is mirrored; U1 notch at pins 1/28.
Prototype: firmware and physical assembly tests pending. See PCB_REVIEW.md.
Power pins on source connectors describe external supplies; Q1 collector is switched power output.

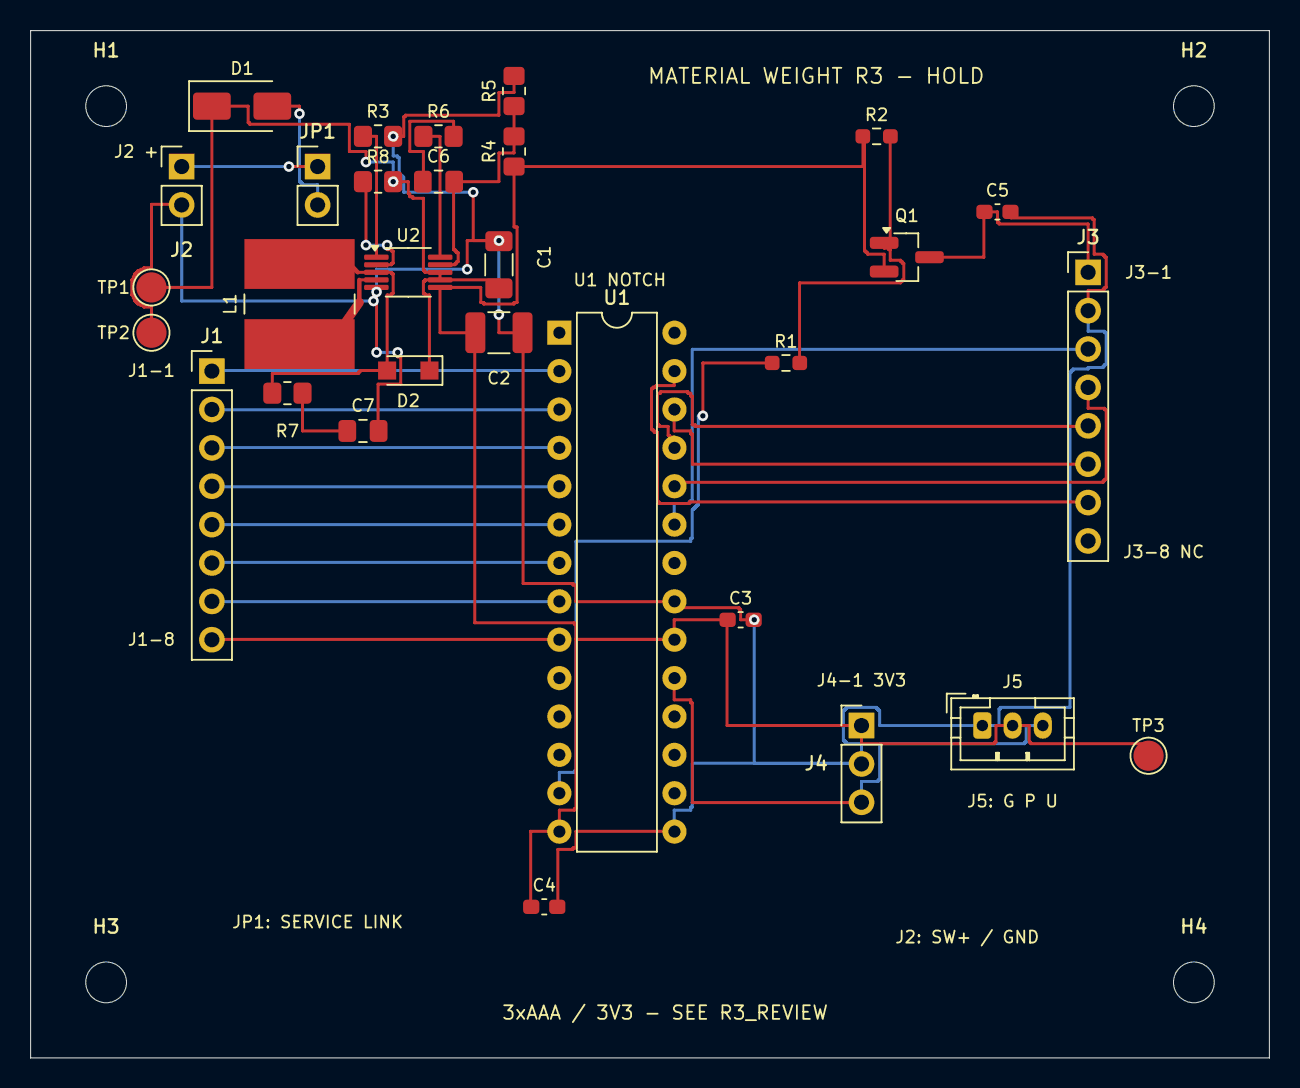
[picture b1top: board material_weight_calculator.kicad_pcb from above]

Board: 2 copper layers, 82.0 x 68.0 mm, 34 parts (0 on the bottom side), 30 nets.

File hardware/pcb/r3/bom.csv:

Reference,Value,Footprint,ManufacturerPartNumber
U1,AVR128DA28-I/SP,MW_footprints:DIP-28_W7.62mm,
J1,KEYPAD_8PIN,MW_footprints:PinHeader_1x08_P2.54mm_Vertical,
J2,SWITCHED_3AAA_IN,MW_footprints:PinHeader_1x02_P2.54mm_Vertical,
JP1,MASTER_LINK,MW_footprints:PinHeader_1x02_P2.54mm_Vertical,
J3,UC1701_ADAPTER_CABLE,MW_footprints:PinHeader_1x08_P2.54mm_Vertical,
J4,UPDI_3V3,MW_footprints:PinHeader_1x03_P2.54mm_Vertical,
H1,M2.5,MW_footprints:MountingHole_2.7mm_M2.5,
H2,M2.5,MW_footprints:MountingHole_2.7mm_M2.5,
H3,M2.5,MW_footprints:MountingHole_2.7mm_M2.5,
H4,M2.5,MW_footprints:MountingHole_2.7mm_M2.5,
U2,LTC3440EMS#PBF,MW_footprints:MSOP-10_3x3mm_P0.5mm,LTC3440EMS#PBF
L1,10uH,MW_footprints:L_CDRH6D38_HandSolder,CDRH6D38NP-100NC
D1,SS14,MW_footprints:D_SMA,SS14
C1,10uF 25V X7R,MW_footprints:C_1206_3216Metric_Pad1.33x1.80mm_HandSolder,GRM31CR71E106KA12L
C2,22uF 25V X7R,MW_footprints:C_1210_3225Metric_Pad1.33x2.70mm_HandSolder,GRM32ER71E226KE15L
R3,60.4k 1%,MW_footprints:R_0805_2012Metric_Pad1.20x1.40mm_HandSolder,RC0805FR-0760K4L
R4,340k 1%,MW_footprints:R_0805_2012Metric_Pad1.20x1.40mm_HandSolder,RC0805FR-07340KL
R5,200k 1%,MW_footprints:R_0805_2012Metric_Pad1.20x1.40mm_HandSolder,RC0805FR-07200KL
R6,15k 1%,MW_footprints:R_0805_2012Metric_Pad1.20x1.40mm_HandSolder,RC0805FR-0715KL
C6,1.5nF C0G 50V,MW_footprints:C_0805_2012Metric_Pad1.18x1.45mm_HandSolder,GRM2165C1H152JA01D
R8,0R,MW_footprints:R_0805_2012Metric_Pad1.20x1.40mm_HandSolder,RC0805JR-070RL
D2,PMEG2010ER,MW_footprints:Nexperia_CFP3_SOD-123W,"PMEG2010ER,115"
R7,2R 1%,MW_footprints:R_0805_2012Metric_Pad1.20x1.40mm_HandSolder,RC0805FR-072RL
C7,1nF C0G 50V,MW_footprints:C_0805_2012Metric_Pad1.18x1.45mm_HandSolder,GRM2165C1H102JA01D
TP1,VIN,MW_footprints:TestPoint_Pad_D2.0mm,
TP2,GND,MW_footprints:TestPoint_Pad_D2.0mm,
TP3,+3V3,MW_footprints:TestPoint_Pad_D2.0mm,
C3,100nF 25V X7R,MW_footprints:C_0603_1608Metric_Pad1.08x0.95mm_HandSolder,GRM188R71E104KA01D
C4,100nF 25V X7R,MW_footprints:C_0603_1608Metric_Pad1.08x0.95mm_HandSolder,GRM188R71E104KA01D
C5,2.2uF 25V X5R,MW_footprints:C_0603_1608Metric_Pad1.08x0.95mm_HandSolder,GRM188R61E225KA12D
R1,10k 1%,MW_footprints:R_0603_1608Metric_Pad0.98x0.95mm_HandSolder,RC0603FR-0710KL
R2,100k 1%,MW_footprints:R_0603_1608Metric_Pad0.98x0.95mm_HandSolder,RC0603FR-07100KL
Q1,MMBT3906LT1G,MW_footprints:SOT-23_Handsoldering,MMBT3906LT1G
J5,UPDI_JST_PH_2MM,MW_footprints:JST_PH_B3B-PH-K_1x03_P2.00mm_Vertical,B3B-PH-K-S(LF)(SN)
